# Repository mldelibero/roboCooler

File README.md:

# roboCooler

The compiler used is Keil UV5, which can be downloaded at: 
https://www.keil.com/demo/eval/arm.htm

This project is targeted at the STM32F4DISCOVERY developement kit.
http://www.st.com/web/catalog/tools/FM116/CL1620/SC959/SS1532/LN1848/PF252419?s_searchtype=partnumber

You can find the USB driver for the board there if it doesn't install automatically.

In order to compile the code, open up Keil and press F7 or click Project->Build Target

In order to download the code to the board click Flash->Download

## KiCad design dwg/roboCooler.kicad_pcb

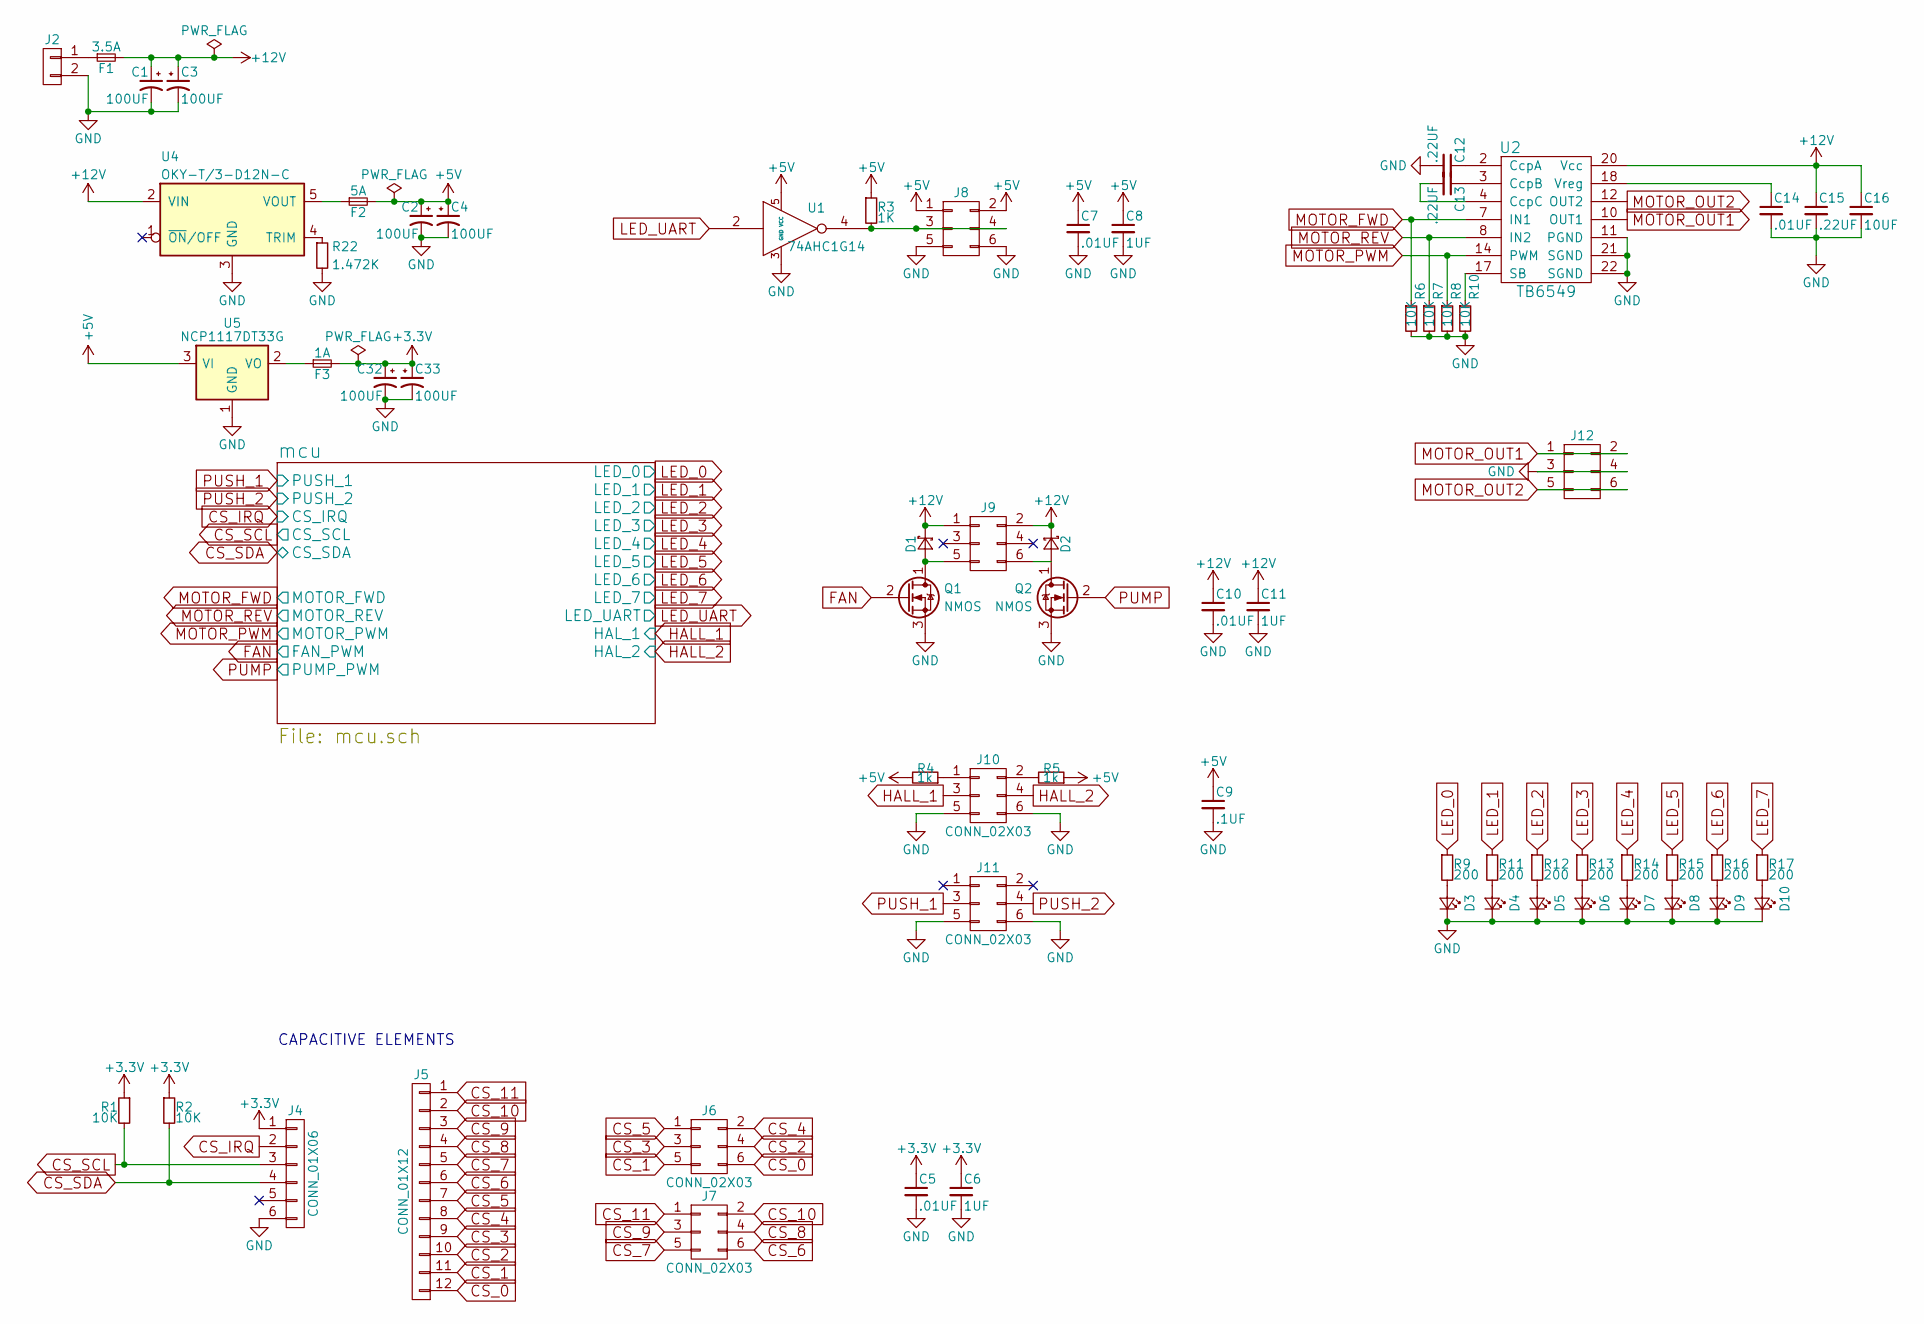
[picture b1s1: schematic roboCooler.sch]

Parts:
C1, C2, C3, C4, C32, C33: 100UF; c_elec_6.6x6.6
C5, C7, C10, C14: .01UF; C_0603_HandSoldering
C6, C8, C11: 1UF; C_0603_HandSoldering
C9: .1UF; C_0603_HandSoldering
C12, C13, C15: .22UF; C_0603_HandSoldering
C16: 10UF; C_0603_HandSoldering
D1, D2: BAT42; SOD-123
D3, D4, D5, D6, D7, D8, D9, D10: LED_Small; D_0805
F1: 3.5A; R_0603_HandSoldering
F2: 5A; R_0603_HandSoldering
F3: 1A; R_0603_HandSoldering
J2: CONN_01X02; OnShore_EDST_02x01_5.08mm_90Deg
J4: CONN_01X06; Socket_Strip_Straight_1x06
J5: CONN_01X12; Socket_Strip_Straight_1x12
J6, J7, J8, J9, J10, J11, J12: CONN_02X03; Molex_CGridIII_02x03_2.54mm
Q1, Q2: NMOS; TO-252-2Lead
R1, R2, R6, R7, R8, R10: 10K; R_0603_HandSoldering
R3: 1K; R_0603_HandSoldering
R4, R5: 1k; R_0603_HandSoldering
R9, R11, R12, R13, R14, R15, R16, R17: 200; R_0603_HandSoldering
R22: 1.472K; R_0603_HandSoldering
U1: 74AHC1G14; SOT-23-5
U2: TB6549
U4: OKY-T/3-D12N-C; OKY-T3
U5: NCP1117DT33G; TO-252-2

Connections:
+3V3: C5.1, C6.1, C32.1, C33.1, F3.2, J4.1, R1.1, R2.1; also elsewhere on the board
+5V: C2.1, C4.1, C7.1, C8.1, C9.1, F2.2, J8.1, J8.2, R3.1, R4.2, R5.1, U1.5 (VCC), U5.3 (VI)
+12V: C1.1, C3.1, C10.1, C11.1, C15.1, C16.1, D1.1 (K), D2.1 (K), F1.2, J9.1, J9.2, U2.20 (Vcc), U4.2 (VIN)
CS_0: J5.12, J6.6
CS_1: J5.11, J6.5
CS_2: J5.10, J6.4
CS_3: J5.9, J6.3
CS_4: J5.8, J6.2
CS_5: J5.7, J6.1
CS_6: J5.6, J7.6
CS_7: J5.5, J7.5
CS_8: J5.4, J7.4
CS_9: J5.3, J7.3
CS_10: J5.2, J7.2
CS_11: J5.1, J7.1
CS_IRQ: J4.2; also elsewhere on the board
CS_SCL: J4.3, R1.2; also elsewhere on the board
CS_SDA: J4.4, R2.2; also elsewhere on the board
FAN: Q1.2 (G); also elsewhere on the board
GND: C1.2, C2.2, C3.2, C4.2, C5.2, C6.2, C7.2, C8.2, C9.2, C10.2, C11.2, C12.2, C14.2, C15.2, C16.2, C32.2, C33.2, D3.1 (K), D4.1 (K), D5.1 (K), D6.1 (K), D7.1 (K), D8.1 (K), D9.1 (K), D10.1 (K), J2.2, J4.6, J8.5, J8.6, J10.5, J10.6, J11.5, J11.6, J12.3, J12.4, Q1.3 (S), Q2.3 (S), R6.2, R7.2, R8.2, R10.2, R22.2, U1.3 (GND), U2.11 (PGND), U2.21 (SGND), U2.22 (SGND), U4.3 (GND), U5.1 (GND); also elsewhere on the board
HALL_1: J10.3; also elsewhere on the board
HALL_2: J10.4; also elsewhere on the board
LED_0: R9.1; also elsewhere on the board
LED_1: R11.1; also elsewhere on the board
LED_2: R12.1; also elsewhere on the board
LED_3: R13.1; also elsewhere on the board
LED_4: R14.1; also elsewhere on the board
LED_5: R15.1; also elsewhere on the board
LED_6: R16.1; also elsewhere on the board
LED_7: R17.1; also elsewhere on the board
LED_UART: U1.2; also elsewhere on the board
MOTOR_FWD: R6.1, U2.7 (IN1); also elsewhere on the board
MOTOR_OUT1: J12.1, J12.2, U2.10 (OUT1)
MOTOR_OUT2: J12.5, J12.6, U2.12 (OUT2)
MOTOR_PWM: R8.1, U2.14 (PWM); also elsewhere on the board
MOTOR_REV: R7.1, U2.8 (IN2); also elsewhere on the board
unnamed: C12.1, U2.2 (CcpA)
unnamed: C13.1, U2.3 (CcpB)
unnamed: C13.2, U2.4 (CcpC)
unnamed: C14.1, U2.18 (Vreg)
unnamed: D1.2 (A), J9.5, Q1.1 (D)
unnamed: D2.2 (A), J9.6, Q2.1 (D)
unnamed: D3.2 (A), R9.2
unnamed: D4.2 (A), R11.2
unnamed: D5.2 (A), R12.2
unnamed: D6.2 (A), R13.2
unnamed: D7.2 (A), R14.2
unnamed: D8.2 (A), R15.2
unnamed: D9.2 (A), R16.2
unnamed: D10.2 (A), R17.2
unnamed: F1.1, J2.1
unnamed: F2.1, U4.5 (VOUT)
unnamed: F3.1, U5.2 (VO)
unnamed: J8.3, J8.4, R3.2, U1.4
unnamed: J10.1, R4.1
unnamed: J10.2, R5.2
unnamed: R10.1, U2.17 (SB)
unnamed: R22.1, U4.4 (TRIM)
PUMP: Q2.2 (G); also elsewhere on the board
PUSH_1: J11.3; also elsewhere on the board
PUSH_2: J11.4; also elsewhere on the board

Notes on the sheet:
CAPACITIVE ELEMENTS

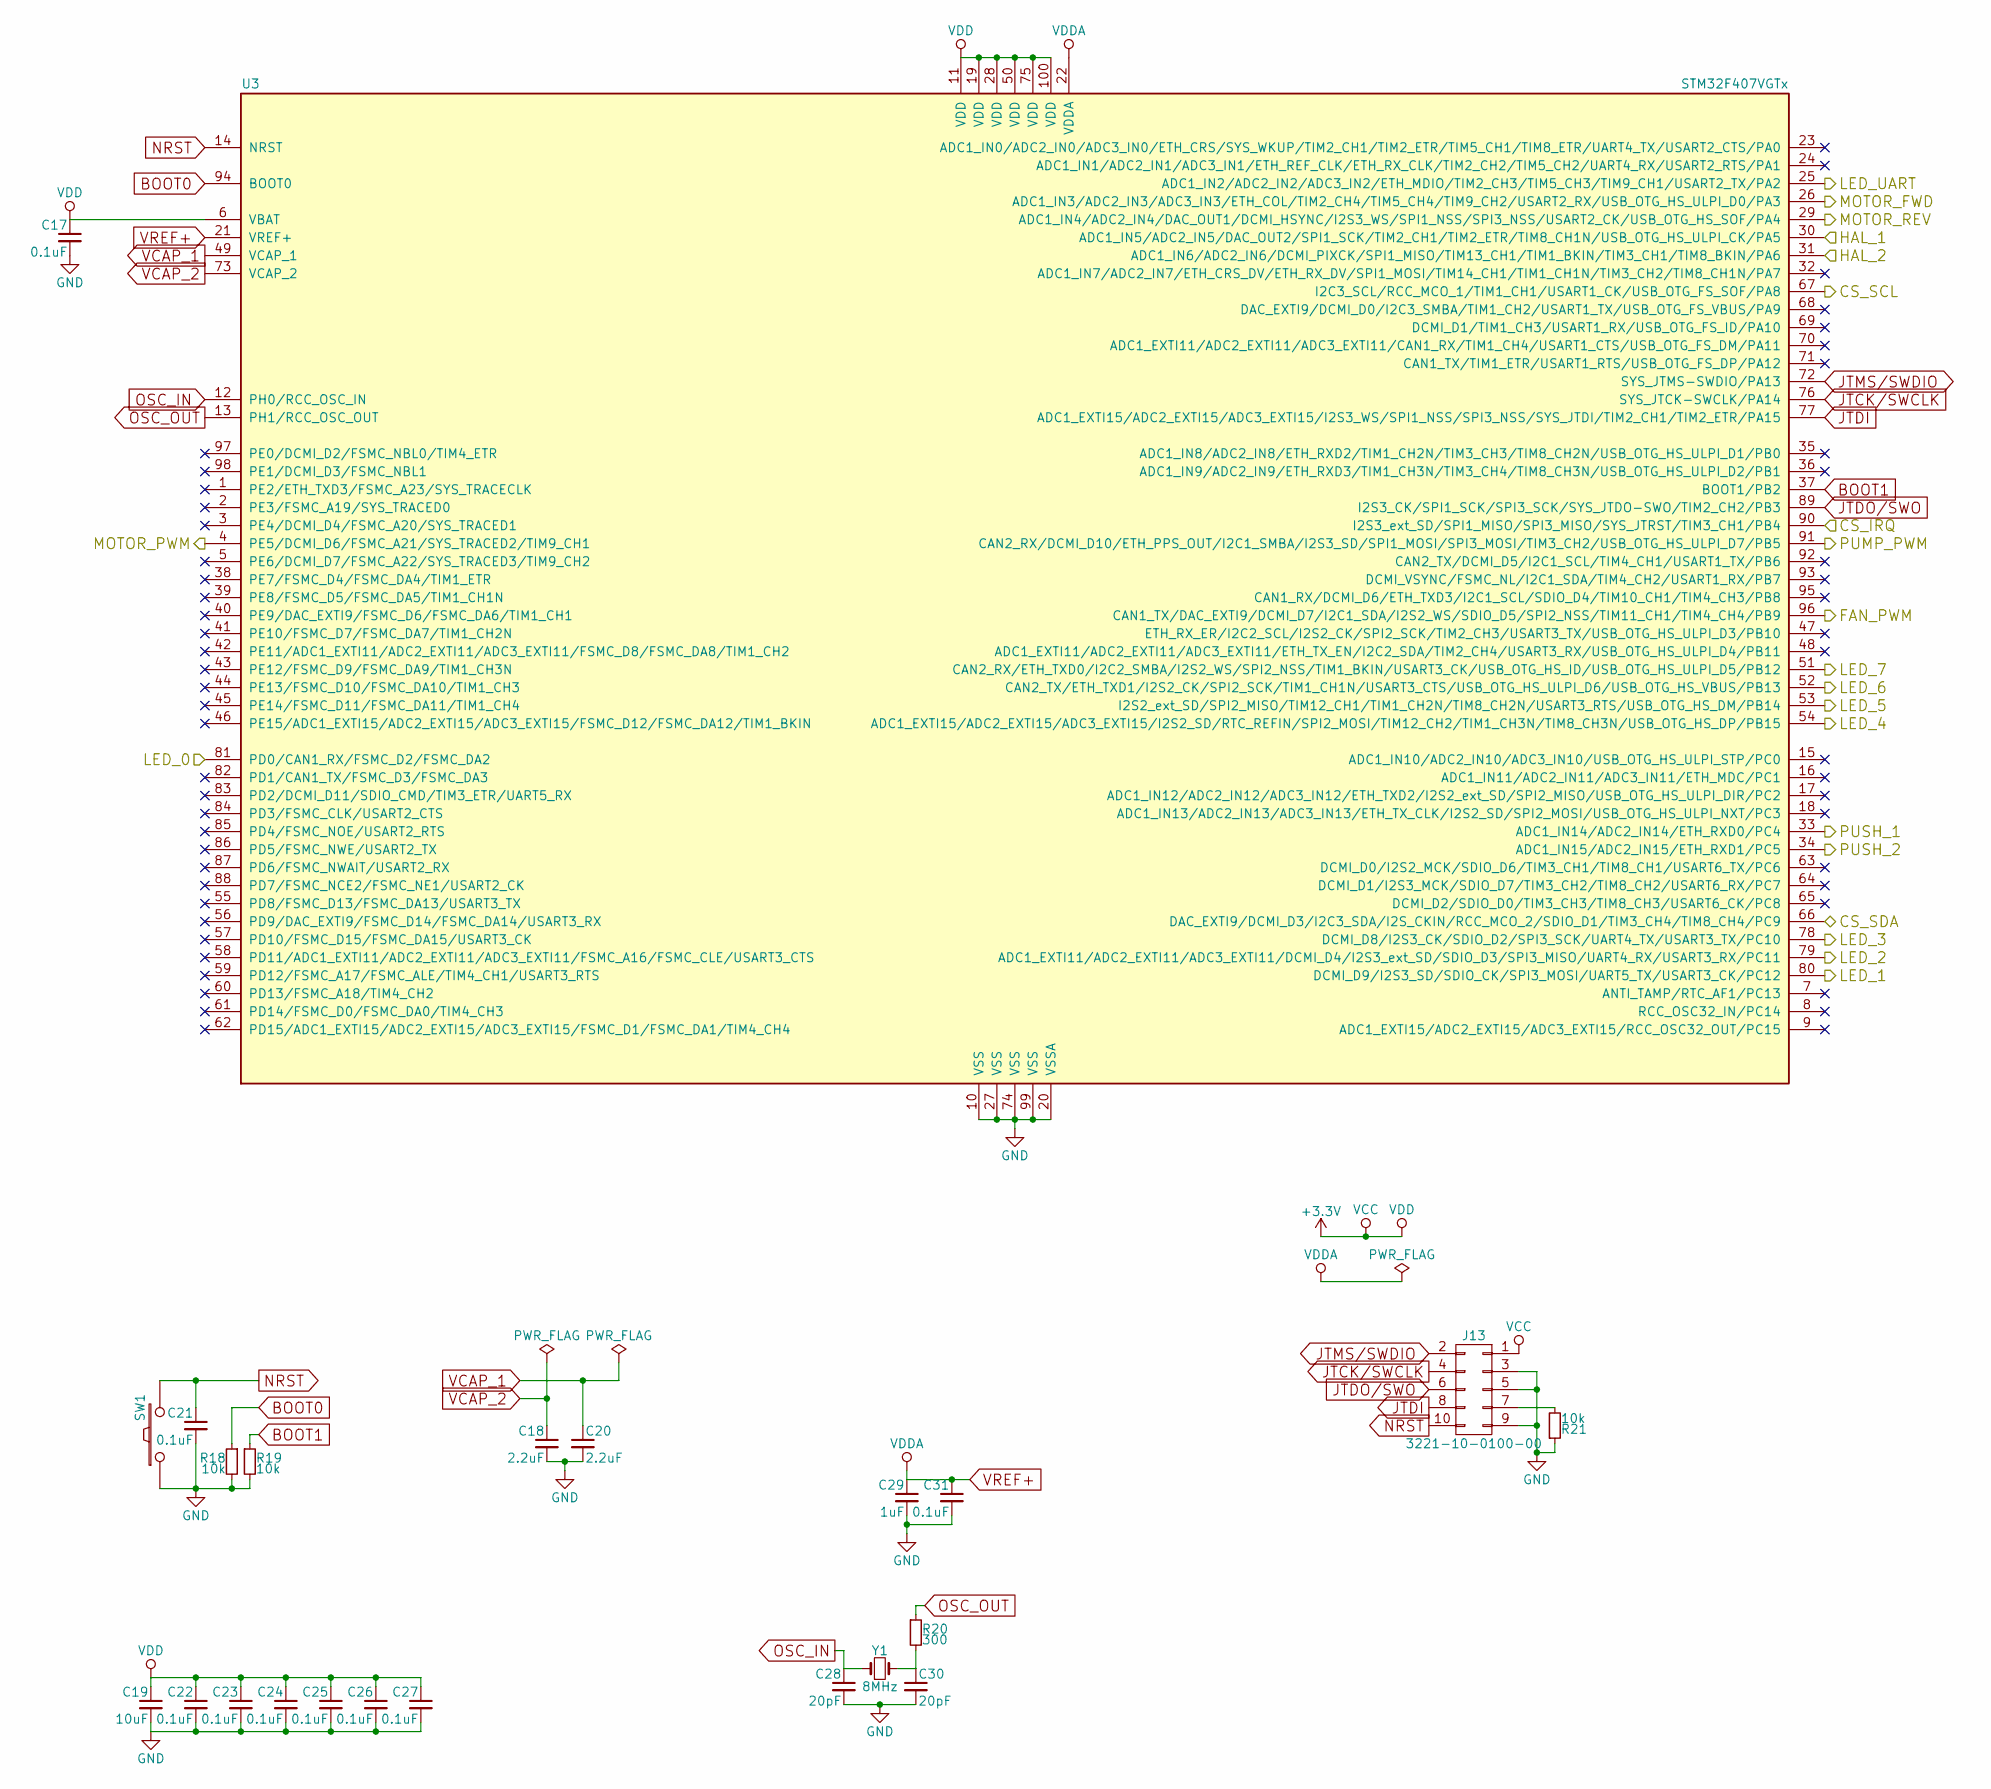
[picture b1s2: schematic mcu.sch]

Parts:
C17, C21, C22, C23, C24, C25, C26, C27, C31: 0.1uF; C_0603_HandSoldering
C18, C20: 2.2uF; C_0603_HandSoldering
C19: 10uF; C_0603_HandSoldering
C28, C30: 20pF; C_0603_HandSoldering
C29: 1uF; C_0603_HandSoldering
J13: 3221-10-0100-00; Header_02x05_50mil
R18, R19, R21: 10k; R_0603_HandSoldering
R20: 300; R_0603_HandSoldering
SW1: TL3342; SW_SPST_TL3342
U3: STM32F407VGTx; LQFP-100_14x14mm_Pitch0.5mm
Y1: 8MHz; Crystal_SMD_Abracon_ABM3-2pin_5.0x3.2mm_HandSoldering; Part Number ABM3-8.000MHZ-D2Y-T

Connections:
+3V3: C17.1, C19.1, C22.1, C23.1, C24.1, C25.1, C26.1, C27.1, J13.1, U3.6 (VBAT), U3.11 (VDD), U3.19 (VDD), U3.28 (VDD), U3.50 (VDD), U3.75 (VDD), U3.100 (VDD); also elsewhere on the board
BOOT0: R18.1, U3.94 (BOOT0)
BOOT1: R19.1, U3.37 (BOOT1/PB2)
CS_IRQ: U3.90 (I2S3_ext_SD/SPI1_MISO/SPI3_MISO/SYS_JTR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); also elsewhere on the board
CS_SCL: U3.67 (I2C3_SCL/RCC_MCO_1/TIM1_CH1/USART1_CK/U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); also elsewhere on the board
CS_SDA: U3.66 (DAC_EXTI9/DCMI_D3/I2C3_SDA/I2S_CKIN/RCC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); also elsewhere on the board
FAN: U3.96 (CAN1_TX/DAC_EXTI9/DCMI_D7/I2C1_SDA/I2S2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); also elsewhere on the board
GND: C17.2, C18.2, C19.2, C20.2, C21.2, C22.2, C23.2, C24.2, C25.2, C26.2, C27.2, C28.2, C29.2, C30.2, C31.2, J13.3, J13.5, J13.9, R18.2, R19.2, R21.1, SW1.1, U3.10 (VSS), U3.20 (VSSA), U3.27 (VSS), U3.74 (VSS), U3.99 (VSS); also elsewhere on the board
HALL_1: U3.30 (ADC1_IN5/ADC2_IN5/DAC_OUT2/SPI1_SCK/TIM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); also elsewhere on the board
HALL_2: U3.31 (ADC1_IN6/ADC2_IN6/DCMI_PIXCK/SPI1_MISO/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); also elsewhere on the board
JTCK/SWCLK: J13.4, U3.76 (SYS_JTCK-SWCLK/PA14)
JTDI: J13.8, U3.77 (ADC1_EXTI15/ADC2_EXTI15/ADC3_EXTI15/I2S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)
JTDO/SWO: J13.6, U3.89 (I2S3_CK/SPI1_SCK/SPI3_SCK/SYS_JTDO-SWO/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)
JTMS/SWDIO: J13.2, U3.72 (SYS_JTMS-SWDIO/PA13)
LED_0: U3.81 (PD0/CAN1_RX/FSMC_D2/FSMC_DA2); also elsewhere on the board
LED_1: U3.80 (DCMI_D9/I2S3_SD/SDIO_CK/SPI3_MOSI/UART5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); also elsewhere on the board
LED_2: U3.79 (ADC1_EXTI11/ADC2_EXTI11/ADC3_EXTI11/DCM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); also elsewhere on the board
LED_3: U3.78 (DCMI_D8/I2S3_CK/SDIO_D2/SPI3_SCK/UART4_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); also elsewhere on the board
LED_4: U3.54 (ADC1_EXTI15/ADC2_EXTI15/ADC3_EXTI15/I2S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); also elsewhere on the board
LED_5: U3.53 (I2S2_ext_SD/SPI2_MISO/TIM12_CH1/TIM1_CH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); also elsewhere on the board
LED_6: U3.52 (CAN2_TX/ETH_TXD1/I2S2_CK/SPI2_SCK/TIM1_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); also elsewhere on the board
LED_7: U3.51 (CAN2_RX/ETH_TXD0/I2C2_SMBA/I2S2_WS/SPI2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); also elsewhere on the board
LED_UART: U3.25 (ADC1_IN2/ADC2_IN2/ADC3_IN2/ETH_MDIO/TIM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); also elsewhere on the board
MOTOR_FWD: U3.26 (ADC1_IN3/ADC2_IN3/ADC3_IN3/ETH_COL/TIM2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); also elsewhere on the board
MOTOR_PWM: U3.4 (PE5/DCMI_D6/FSMC_A21/SYS_TRACED2/TIM9_C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); also elsewhere on the board
MOTOR_REV: U3.29 (ADC1_IN4/ADC2_IN4/DAC_OUT1/DCMI_HSYNC/I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); also elsewhere on the board
NRST: C21.1, J13.10, SW1.2, U3.14 (NRST)
unnamed: C30.1, R20.2, Y1.2
unnamed: J13.7, R21.2
OSC_IN: C28.1, U3.12 (PH0/RCC_OSC_IN), Y1.1
OSC_OUT: R20.1, U3.13 (PH1/RCC_OSC_OUT)
PUMP: U3.91 (CAN2_RX/DCMI_D10/ETH_PPS_OUT/I2C1_SMBA/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); also elsewhere on the board
PUSH_1: U3.33 (ADC1_IN14/ADC2_IN14/ETH_RXD0/PC4); also elsewhere on the board
PUSH_2: U3.34 (ADC1_IN15/ADC2_IN15/ETH_RXD1/PC5); also elsewhere on the board
VCAP_1: C20.1, U3.49 (VCAP_1)
VCAP_2: C18.1, U3.73 (VCAP_2)
VREF+: C29.1, C31.1, U3.21 (VREF+), U3.22 (VDDA)

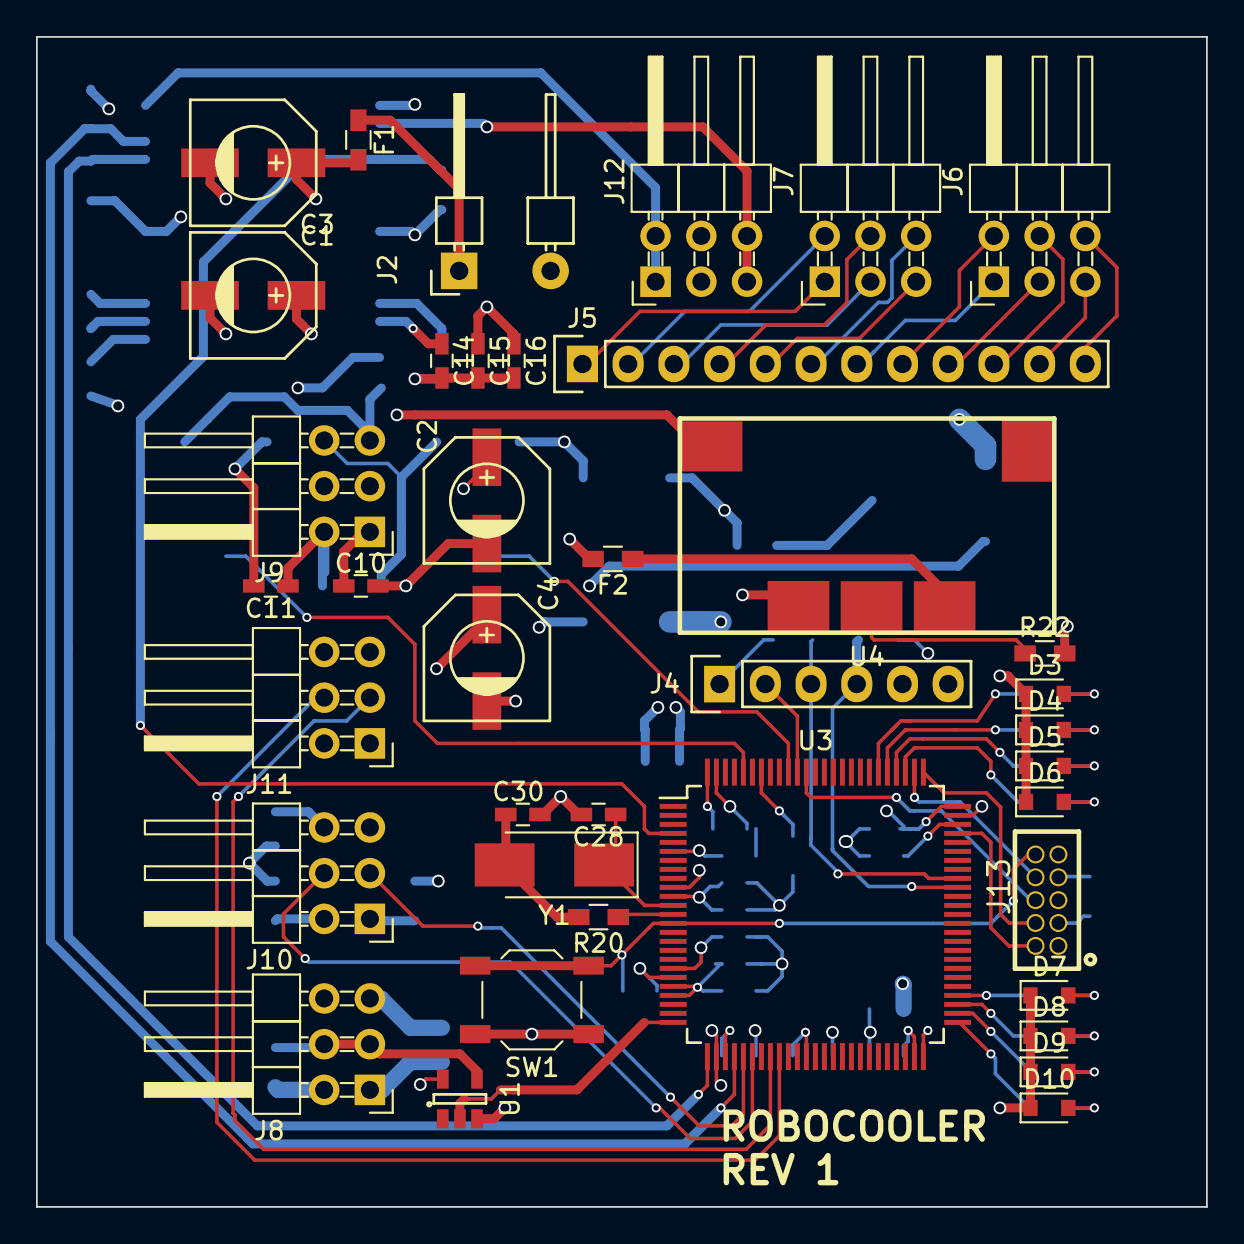
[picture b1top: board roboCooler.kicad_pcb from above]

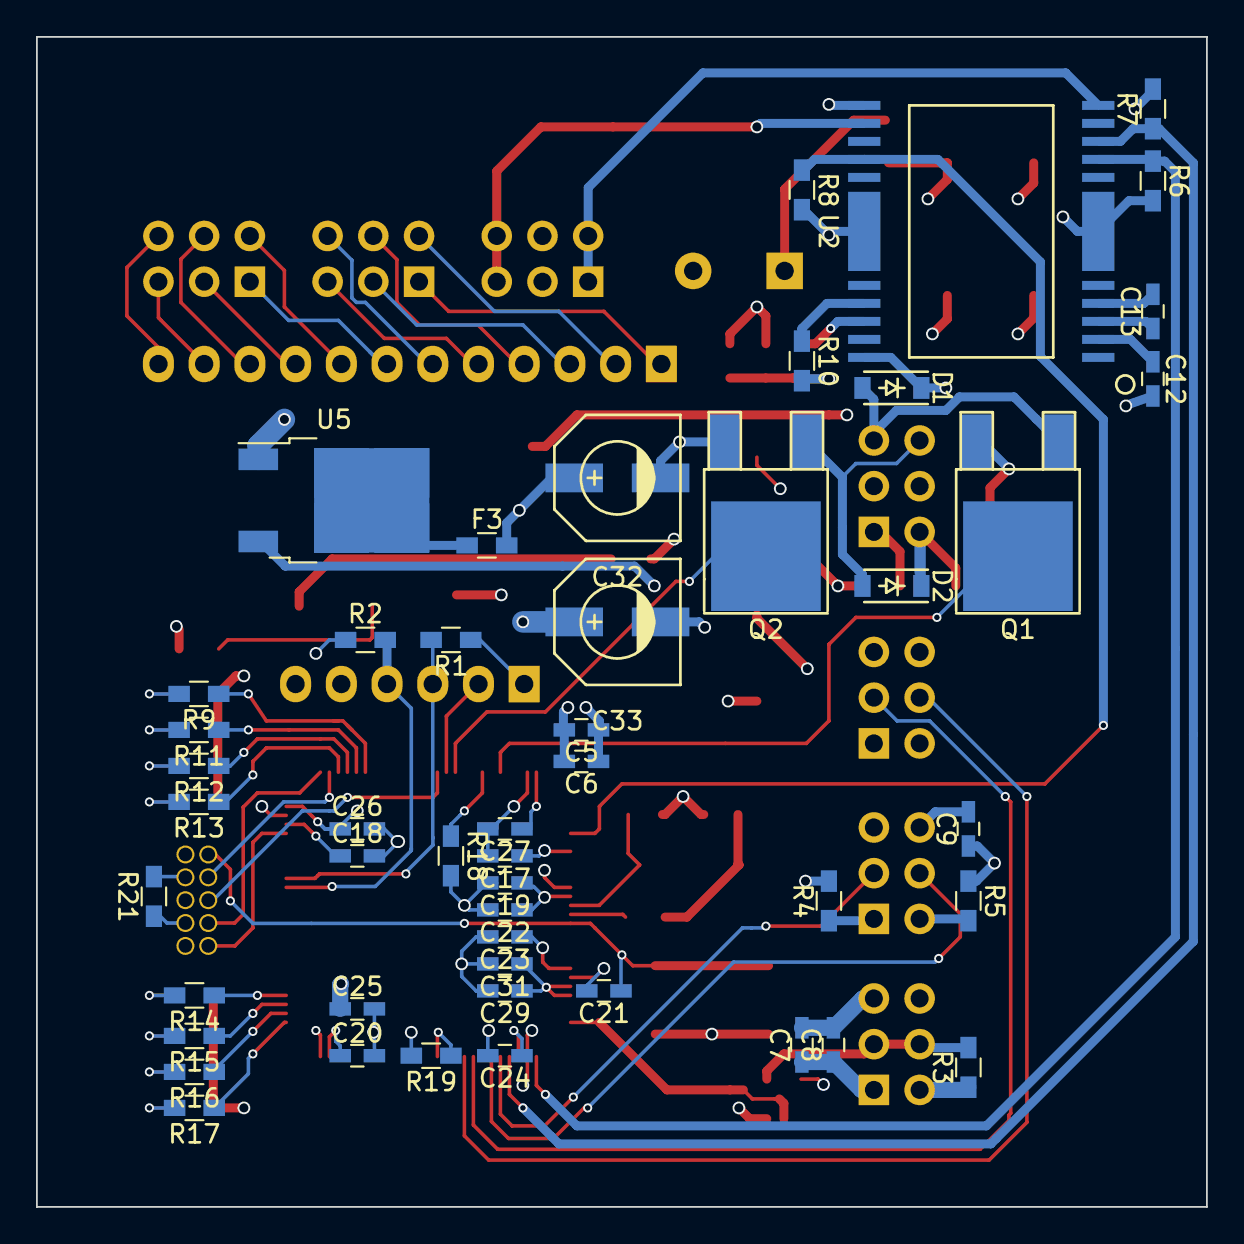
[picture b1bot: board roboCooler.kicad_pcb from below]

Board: 4 copper layers, 65.0 x 65.0 mm, 88 parts (49 on the bottom side), 75 nets.

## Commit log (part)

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2010-09-16 updated for pushbuttons
2015-09-21 added library files for gpio
2015-09-21 added main
2015-09-26 added files for scheduler
2015-10-04 first compile
2015-10-06 recreated prj file b/c it wouldnt open.
2015-10-06 added heartbeart led
2015-10-10 Sched is working at 1kHz Heartbeat is working at 1Hz Test toggle is working.
2015-10-10 updated clock config
2015-10-10 added reference manual for processor
2015-10-10 fixed documentation naming
2015-10-24 added libraries for led driver
2015-10-24 added doc for led driver chip
2015-10-24 added leds and library files
2015-10-24 added MWE for LED driver
2015-11-14 updated led driver
2015-11-15 added capacitor sense files
2015-11-15 added crossbar for selecting mcu pins
2015-11-18 defined HSE_VALUE at 8MHz
2015-11-18 added capsense i2c and dma files to prj
2015-11-25 added cap touch app note
2015-11-25 updated proj file
2015-12-05 added docs for hall sensor
2015-12-05 combined src and inc dirs
2015-12-05 added pin doc to usart output.
2015-12-05 Added base for lid motor driver.
2015-12-06 Added capsense to proj file. moved .h file to src dir.
2015-12-06 added drawing files for schematic purposes.
2015-12-06 added bom
2015-12-07 moved scheduler to tim4 to accomodate conseq timers for the pwm outputs.
2015-12-07 added basic information for all of the connections
2015-12-23 updated hbridge
2016-01-16 moved hbridge to second sheet.
2016-01-16 added resistors for hbridge optocouplers
2016-01-18 Added connectors to BOM
2016-02-14 moved lid motor and push button pins
2016-02-14 added documentation for some parts
2016-03-20 moved for tdd
2016-03-20 Dont need to specify tests
2016-03-20 started a test for time
2016-03-20 moved timeTest to appropriate dir
2016-03-21 moved all mcu code to ./code dir
2016-03-21 changed from giving timer ptr to timer index
2016-03-21 added line to uncomment to allow warnings
2016-04-01 Changed CPPUTEST_HOME to work with either env var or use in makefile added mockFiles to testSrc
2016-04-01 chagned Time to Timer
2016-04-02 added files for integration testing of timerDriver
2016-04-02 updated to use interrupt.
2016-04-23 updated name for setting up int test of timer driver
2016-04-23 added tmp directory to ignore
2016-04-23 added cached symbol library
2016-04-23 added tests for integration of timer driver
2016-04-23 updated to source
2016-04-23 fixed error in Makefile
2016-04-24 moved prj dir under code dir
2016-04-24 moved timer vars to own dir to move out of the way for most testing.
2016-04-24 moved timer tests to own dirs
2016-04-25 added some testing for pb filtering
2016-04-30 combining integration testing of timer driver and timer.
2016-04-30 moved integration test files to dir seperate from temp files
2016-04-30 added new dir for testing integration code
2016-04-30 added code to test init fun for timer test
2016-04-30 condensed setting mock call order var to one place
2016-04-30 moved stdlib mocks to own subdir under mock
2016-05-01 added tests for timer isr and isTimerExpired fun.
2016-06-18 added pb code and tests
2016-06-18 added pb integration test
2016-06-19 Added pushbuttons to layout
2016-06-19 added pull up resistors to cap sense i2c lines
2016-06-19 added bak files to ignore list
2016-06-19 Added LED USART to layout
2016-06-19 added temporary excel files to the ignore list
2016-06-20 fixed cap sense conn gender footprint
2016-06-20 added pump parts to layout
2016-06-21 fixed connector 3d view on board.
2016-06-29 added motor driver chip to schematic and removed hbridge
2016-07-03 placed components for motor driver
2016-07-03 added pull up resistors to hall effect sensors
2016-07-04 updated power nets on schematic
2016-07-04 updated power entery to baord
2016-07-04 moved crossbar to dwg dir
2016-07-04 synced crossbar with mcu pinout on schematic
2016-07-04 reclassified TB6549 symbol gnd pins as power inputs
2016-07-04 reset layout
2016-07-05 Initial part placement on layout complete
2016-07-06 updated BOM
2016-07-09 updated conn for capsense out and hal sensors
2016-07-10 moved all components inside the disc envelope
2016-07-12 updated pcb design rules
2016-07-12 first pass at layout
2016-07-13 increased size of pcb power nets and reordered some components.
2016-07-14 added mounting holes
2016-07-14 increased trace widths for led driver
2016-07-17 moved J11 to the same 6pin connector.
2016-07-29 tweaked layout before ordering
2016-07-29 added board name, rev, & sn to silkscreen
2016-08-29 added ledDriver files
2016-08-29 removed unnecessary ledDriver defines
2016-08-29 updated test mocks to compile all code with gcc
2016-08-29 confined callOrder var to file scope
2016-08-29 added test to allocate led timer
2016-08-30 created main and added init fun
2016-08-31 timer mock now looking for correct timer when setting a timer added reset for timer mock added ability to mock allocate a specific timer.
2016-08-31 now initializing leds
2016-08-31 now checking that pushbutton sets the correct timer
2016-08-31 now checking that leds sets the correct timer
2016-08-31 moved all driver files to src/drivers and fixed compilation errors
2016-08-31 now keeping track of all mocking all io pins for each GPIOx
2016-09-03 added src & tests to set/clear leds
2016-09-03 moved push button test out of the way for now.
2016-09-03 added component class and tests
2016-09-03 timer.h -- fixed formatting of include protection hash
2016-09-03 shrunk test for execute fun. Added test for initialize fun.
2016-09-03 removed bad check for const calling virtual function
2016-09-03 leds now update hardware on run
2016-09-04 added ability for inherited child to set comp reset time
2016-09-04 added tests for led boot mode operation.
2016-09-10 added gdb flag to make test makefile
2016-09-10 added rest of testing for leds
2016-09-14 included mcu header to compile with keil.
2016-09-14 updated comp executable from full compile
2016-09-14 removed depricated scheduler.* files for timer(driver).* files
2016-09-14 started testing the lid motor
2016-09-14 created makefile to compile all components
2016-09-14 added check for initalizing lidMotor
2016-09-14 added lidmotor driver init test
2016-09-15 added virtual destructor to component base class to be able to delete derived children
2016-09-15 lid motor now uses limit switches to determine state
2016-09-16 added lid reacting to captouch sensor
2016-09-18 restructured tests to allow mock/natural testing implementations hirearchies
2016-09-18 added limit switch initalization to init fun
2016-09-18 removed exe files from repo
2016-09-18 added Level 1 mocks
2016-09-18 added Level1 mocks to makefile
2016-09-18 limsw mock header was overwriting src
2016-09-18 testing that limsw driver returns correct output
2016-09-18 init now initalizes limswitchdriver
2016-09-18 moved lidMotorTest up one level to allow for limitSwitch testing
2016-09-19 limSwitch samples inputs on run
2016-10-18 removed duplicated mock -- see Level_2
2016-10-18 moved timer test from Level_2 to Level_1
2016-10-18 remvoed function pointer from limit switch
2016-10-18 no longer looking at timer during testing
2016-10-18 now using mocks from lower levels
2016-11-20 Added no c++14 flag to be compatible with new cpputest 3.8 build
2016-11-20 added base hardware driver class
2016-11-22 added virt dest to cdriver to be able to delete children.
2016-11-22 moved cdriver init_hardware to be pure virt
2016-11-22 limswDriver -- swapping constructor arguments
2016-11-22 limSwDriver -- added sample, removed old funs, & retested init
2016-11-23 now requiring limitswitch to instantiate with a hardware driver object
2016-12-02 updated limsw for basic functionality
2016-12-04 moving to use mocks for limSw and driver
2016-12-10 added hysteresis to limit switch
2016-12-10 moved mock mock files to single mockFiles directory
2016-12-10 added test dir for the main loop
2016-12-10 added scripts for continual compilation
2016-12-10 now testing module initalization in init()
2016-12-10 tests -- testing reset of limsw obj
2016-12-11 added i2c init to capdriver
2016-12-11 added lid motor to main loop
2016-12-12 doc -- Added app note for cap touch proximity detection
2016-12-12 changed cap touch from Get_TouchDetected to Is_TouchDetected
2016-12-12 Now only cleared touch detected var after customer polls it
2016-12-17 added in cap sense chip initialization routine
2016-12-26 moved init tests to own directory
2016-12-26 updated component makefiles for compilation
2016-12-26 added sensor inputs to ledstrip component
2016-12-26 added ledstrip driver
2016-12-27 added testing and code outline for complete led strip component
2016-12-27 added code for led objs
2016-12-27 led strip comp now always has a timeout of zero
2016-12-27 now testing that we did not use up all available timers in the init function
2016-12-27 scene is no longer derived from component
2016-12-27 added initial test framework for a scene obj
2016-12-27 added basic testing for scene
2016-12-31 main makefile corrected clean and clean all
2017-01-02 Added getting and forcing status of led behavior base class
2017-01-04 reorganized Scene tests so that we are not directly testing the internal state machine
2017-01-05 initializing behavior resets state
2017-01-05 added stop triggering and blending to scene
2017-01-07 Added overloaded component run with void*
2017-01-07 scene keeps behaviors updated with numleds
2017-01-07 scene sends ledobjarray pointer when running behaviors
2017-01-21 moved LED behavior child to a pointer in the test setup
2017-01-21 now testing behavior blending functionality
2017-01-21 renamed component timer vars to be more descriptive
2017-01-21 renamed component var *val* to *period* for clarity
2017-01-21 updated code for behavior time
2017-01-21 now can set ledbeh numleds
2017-01-21 now ignoring stackdumps and notepad
2017-01-22 can operate on a percentage band of the led strip with an led behavior
2017-01-22 refactored HalfOn object
2017-01-22 behaviors can now do additionblending
2017-01-22 moved checking led beh output into a function to be shared between test files
2017-01-25 changed from percentages to indexes and removed set_numleds funs
2017-01-26 simplified checkleds helper functions into one
2017-01-27 removed unused tests
2017-01-28 added test to make sure ledstripdriver is initialized in init fun
2017-01-28 added framework for ledstripdriver tests
2017-01-29 changed ledObj to use float to store percentages
2017-01-30 moved led strip driver level 2 to be able to use mock timer funs
2017-01-30 added testing for ledStrip driver
2017-01-31 updated prj to compile with keil
2017-02-06 added periph pointer conversions to dma driver
2017-02-28 porting to hal -- gpio mostly done
2017-03-01 porting to hal -- tim mostly done
2017-03-01 adding hal i2c lib
2017-03-09 commented most code. Moved timer to HAL and toggling pin in isr
2017-03-19 timer operates at the correct frequency
2017-03-22 limitswitchdriver compiles
2017-03-22 tests now compile for ledDriver
2017-03-22 deleted tmp file
2017-03-22 removed unused include
2017-03-22 started porting level2 -- ledstripdriver compiles but fails a test
2017-03-23 ledtests now run
2017-03-23 led behavior & childred tests now run
2017-03-24 captouchdriver tests now run
2017-03-24 scene now compiles
2017-03-25 ledstriptests pass
2017-03-25 init tests pass
2017-03-25 deleted copied version of mockFiles
2017-03-25 combined common make settings into a single file
2017-04-02 removed unused libs
2017-04-02 added symbolic link to hal lib
2017-04-02 now blinks leds and runs timers
2017-05-07 temporarily hardcoded to test uart dma
2017-05-08 sucessfull scope test of led driver timing
2017-05-13 commit before switching to cmsis
2017-05-13 basic cmsis driver for ledStrip working
2017-05-13 removed unused HAL code and fixed define in RTE_Device for ledStrip
2017-05-13 capsense i2c started to port to cmsis
2017-05-14 reorganized project file list in keil
2017-05-14 started porting lid motor driver to hal
2017-05-15 sample lidMotor output working on scope
2017-05-17 basic test with real motor works. Need to add more bus capacitance
2017-05-17 added hall effect driver to prj
2017-05-17 updated to new version of kicad
2017-05-17 added mcu to board.
2017-05-21 updating board -- no DRC errors
2017-05-23 updated placement on new board. No DRC errors
2017-05-25 added 5V switcher
2017-05-25 added 3.3V LDO
